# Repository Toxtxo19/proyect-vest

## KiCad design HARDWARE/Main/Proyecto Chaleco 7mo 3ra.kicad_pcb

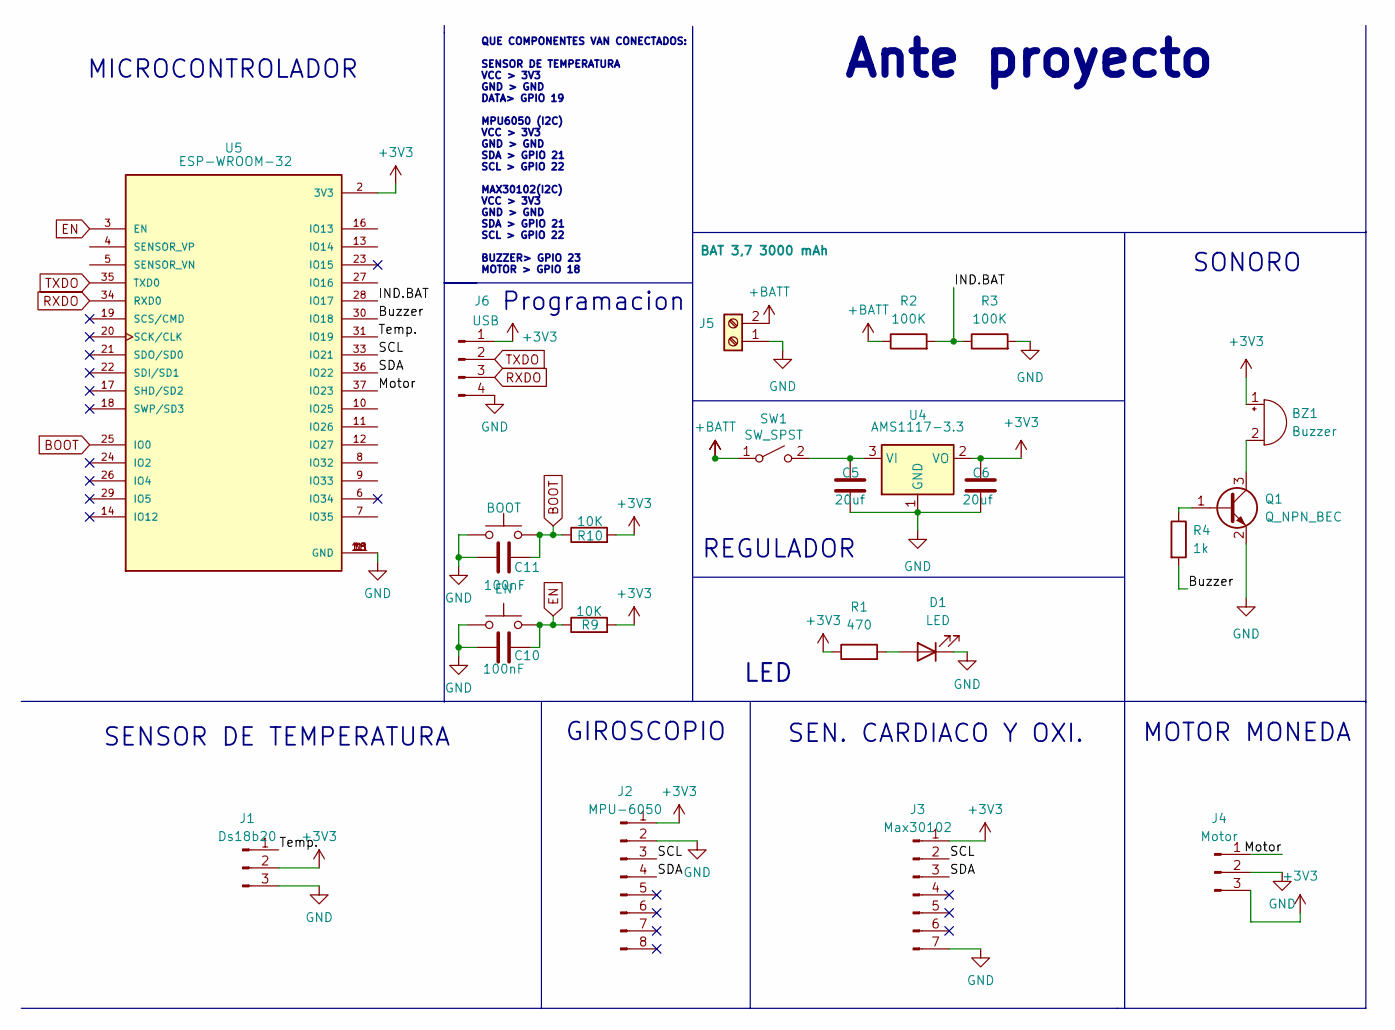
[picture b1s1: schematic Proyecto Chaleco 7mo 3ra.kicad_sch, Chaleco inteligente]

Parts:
BZ1: Buzzer; MagneticBuzzer_PUI_AT-0927-TT-6-R
C5, C6: 20uf; C_0805_2012Metric_Pad1.18x1.45mm_HandSolder
C10, C11: 100nF; C_0805_2012Metric_Pad1.18x1.45mm_HandSolder
D1: LED; LED_0805_2012Metric_Pad1.15x1.40mm_HandSolder
J1: Ds18b20; PinSocket_1x03_P2.54mm_Vertical
J2: MPU-6050; PinSocket_1x08_P2.54mm_Vertical
J3: Max30102; PinSocket_1x07_P2.54mm_Vertical
J4: Motor; PinSocket_1x03_P2.54mm_Vertical
J5: BAT 3,7 3000 mAh; BORNERA2_AZUL
J6: USB; PinHeader_1x04_P2.54mm_Vertical
Q1: Q_NPN_BEC; SOT-23
R1: 470; R_0805_2012Metric_Pad1.20x1.40mm_HandSolder
R2, R3: 100K; R_0805_2012Metric_Pad1.20x1.40mm_HandSolder
R4: 1k; R_0805_2012Metric_Pad1.20x1.40mm_HandSolder
R9, R10: 10K; R_0805_2012Metric_Pad1.20x1.40mm_HandSolder
SW1: SW_SPST; BORNERA2_AZUL
SW3: EN; SW_SPST_CK_RS282G05A3
SW4: BOOT; SW_SPST_CK_RS282G05A3
U4: AMS1117-3.3; SOT-223-3_TabPin2
U5: ESP-WROOM-32; MODULE_ESP-WROOM-32

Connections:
+3V3: BZ1.1 (-), C6.1, J1.2, J2.1, J3.1, J4.3, J6.1, R1.1, R9.2, R10.2, U4.2 (VO), U5.2 (3V3)
+BATT: J5.2, R2.1, SW1.1 (A)
/Buzzer: R4.2, U5.30 (IO18)
/IND.BAT: R2.2, R3.1, U5.28 (IO17)
/Motor: J4.1, U5.37 (IO23)
/SCL: J2.3, J3.2, U5.33 (IO21)
/SDA: J2.4, J3.3, U5.36 (IO22)
/Temp.: J1.1, U5.31 (IO19)
BOOT: C11.1, R10.1, SW4.2, U5.25 (IO0)
EN: C10.1, R9.1, SW3.2, U5.3 (EN)
GND: C5.2, C6.2, C10.2, C11.2, D1.1 (K), J1.3, J2.2, J3.7, J4.2, J5.1, J6.4, Q1.2 (E), R3.2, SW3.1, SW4.1, U4.1 (GND), U5.1 (GND), U5.1.1 (GND), U5.15 (GND), U5.38 (GND)
unnamed: BZ1.2 (+), Q1.3 (C)
unnamed: D1.2 (A), R1.2
unnamed: Q1.1 (B), R4.1
unnamed: C5.1, SW1.2 (B), U4.3 (VI)
RXDO: J6.3, U5.34 (RXD0)
TXDO: J6.2, U5.35 (TXD0)

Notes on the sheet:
QUE COMPONENTES VAN CONECTADOS: SENSOR DE TEMPERATURA VCC > 3V3 GND > GND DATA> GPIO 19 MPU6050 (I2C) VCC > 3V3 GND > GND SDA > GPIO 21 SCL > GPIO 22 MAX30102(I2C) VCC > 3V3 GND > GND SDA > GPIO 21 SCL > GPIO 22 BUZZER> GPIO 23 MOTOR > GPIO 18
LED
MICROCONTROLADOR
MOTOR MONEDA
SEN. CARDIACO Y OXI.
Programacion
SENSOR DE TEMPERATURA
GIROSCOPIO
REGULADOR
Ante proyecto
SONORO

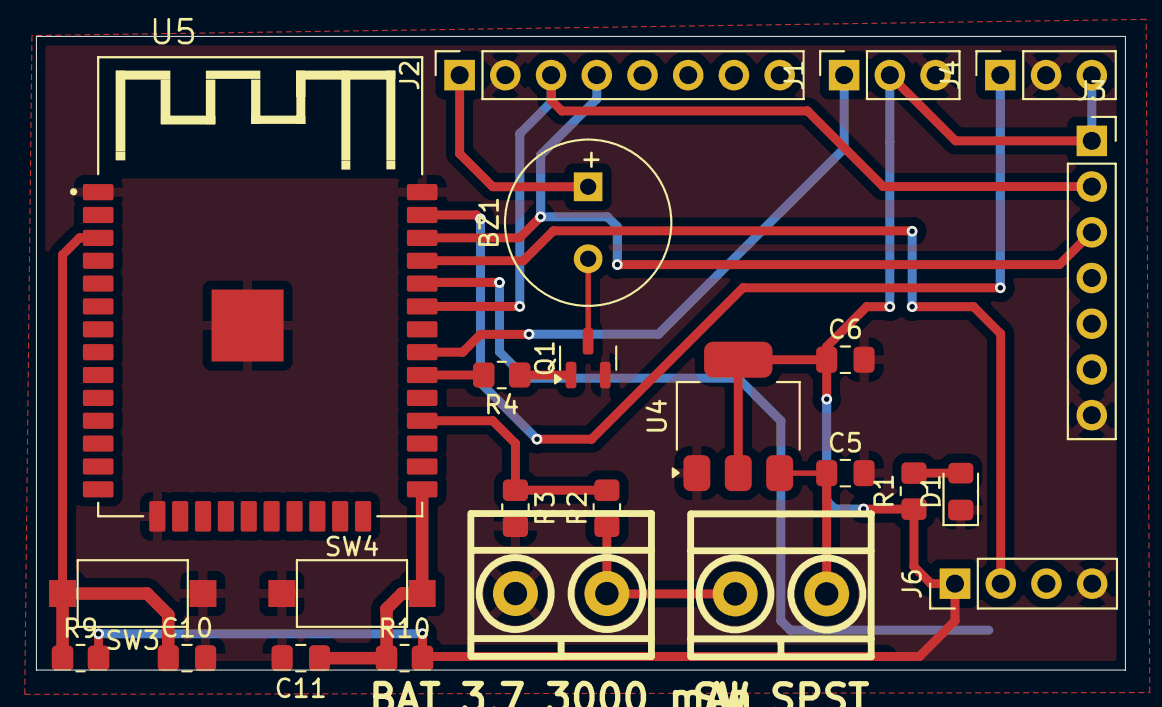
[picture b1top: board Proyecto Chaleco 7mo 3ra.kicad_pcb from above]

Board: 2 copper layers, 60.5 x 35.2 mm, 24 parts (0 on the bottom side), 17 nets.

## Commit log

2026-04-17 inicio
2026-04-29 parte final
